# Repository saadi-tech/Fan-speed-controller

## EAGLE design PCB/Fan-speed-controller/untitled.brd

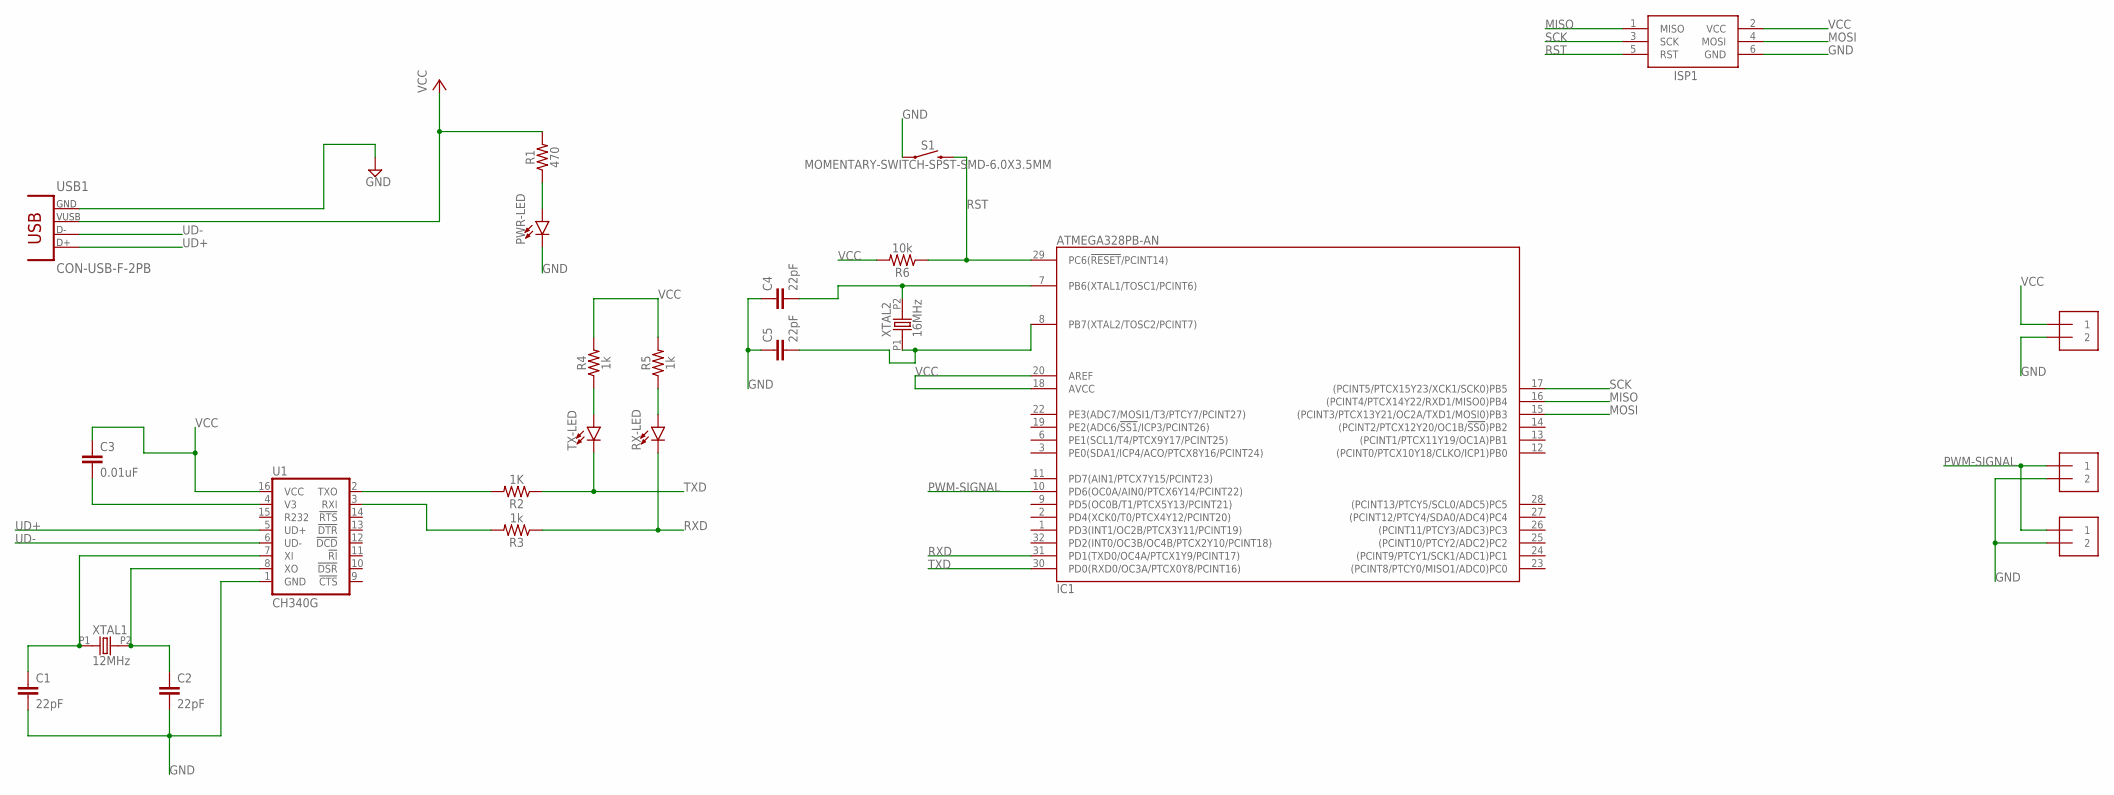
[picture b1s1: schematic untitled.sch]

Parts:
5V/GND: 1X2-3.5MM
C1, C2, C4, C5: 22pF; 0603
C3: 0.01uF; 0603
IC1: ATMEGA328PB-AN; QFP32_7X7_0.80
ISP1: AVRISP-6; AVRISP
MOTOR-1, MOTOR-2: 1X2-3.5MM
PWR-LED: LED1206; LED-1206
R1: 470; 1206
R2: 1K; 1206
R3, R4, R5: 1k; 1206
R6: 10k; 1206
RX-LED: LED1206; LED-1206
S1: MOMENTARY-SWITCH-SPST-SMD-6.0X3.5MM; TACTILE_SWITCH_SMD_6.0X3.5MM
TX-LED: LED1206; LED-1206
U1: CH340G; SO016
USB1: CON-USB-F-2PB; CONN_USB_A_F
XTAL1: 12MHz; HC-49U-PTH
XTAL2: 16MHz; HC-49U-PTH

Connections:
GND: 5V/GND.2, C1.2, C2.2, C4.1, C5.1, IC1.5 (GND), IC1.21 (GND), ISP1.6 (GND), MOTOR-1.2, MOTOR-2.2, PWR-LED.C, S1.1, U1.1 (GND), USB1.4 (GND)
MISO: IC1.16 ((PCINT4/PTCX14Y22/RXD1/MISO0)PB4), ISP1.1 (MISO)
MOSI: IC1.15 ((PCINT3/PTCX13Y21/OC2A/TXD1/MOSI0)PB3), ISP1.4 (MOSI)
unnamed: PWR-LED.A, R1.1
unnamed: C2.1, U1.8 (XO), XTAL1.P2 (2)
unnamed: C1.1, U1.7 (XI), XTAL1.P1 (1)
unnamed: C3.2, U1.4 (V3)
unnamed: R4.1, TX-LED.A
unnamed: R2.2, U1.2 (TXO)
unnamed: R3.2, U1.3 (RXI)
unnamed: C4.2, IC1.7 (PB6(XTAL1/TOSC1/PCINT6)), XTAL2.P2 (2)
unnamed: C5.2, IC1.8 (PB7(XTAL2/TOSC2/PCINT7)), XTAL2.P1 (1)
unnamed: R5.1, RX-LED.A
PWM-SIGNAL: IC1.10 (PD6(OC0A/AIN0/PTCX6Y14/PCINT22)), MOTOR-1.1, MOTOR-2.1
RST: IC1.29 (PC6(!RESET!/PCINT14)), ISP1.5 (RST), R6.1, S1.2
RXD: IC1.31 (PD1(TXD0/OC4A/PTCX1Y9/PCINT17)), R3.1, RX-LED.C
SCK: IC1.17 ((PCINT5/PTCX15Y23/XCK1/SCK0)PB5), ISP1.3 (SCK)
TXD: IC1.30 (PD0(RXD0/OC3A/PTCX0Y8/PCINT16)), R2.1, TX-LED.C
UD+: U1.5 (UD+), USB1.3 (D+)
UD-: U1.6 (UD-), USB1.2 (D-)
VCC: 5V/GND.1, C3.1, IC1.4 (VCC), IC1.18 (AVCC), IC1.20 (AREF), ISP1.2 (VCC), R1.2, R4.2, R5.2, R6.2, U1.16 (VCC), USB1.1 (VUSB)

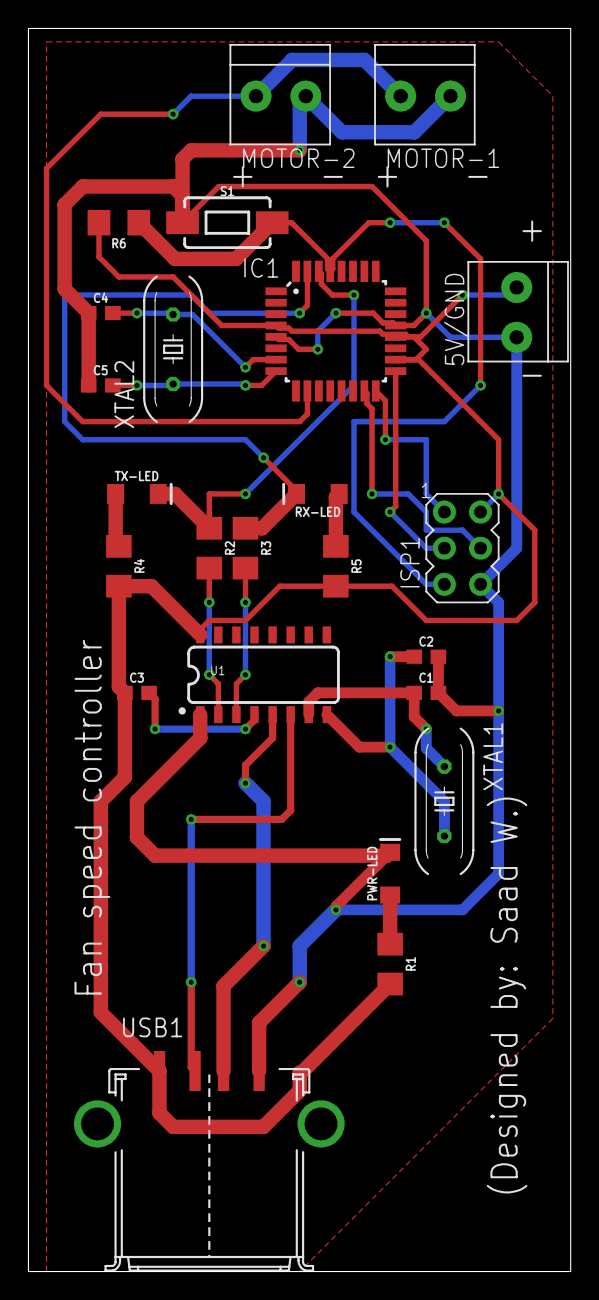
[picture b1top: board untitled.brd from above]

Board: 2 copper layers, 38.1 x 87.3 mm, 24 parts (0 on the bottom side), 21 nets.

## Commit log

2020-11-12 B design done..

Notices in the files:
parts and their libraries:
SparkFun-Capacitors: Licensing: Creative Commons ShareAlike 4.0 International - https://creativecommons.org/licenses/by-sa/4.0
